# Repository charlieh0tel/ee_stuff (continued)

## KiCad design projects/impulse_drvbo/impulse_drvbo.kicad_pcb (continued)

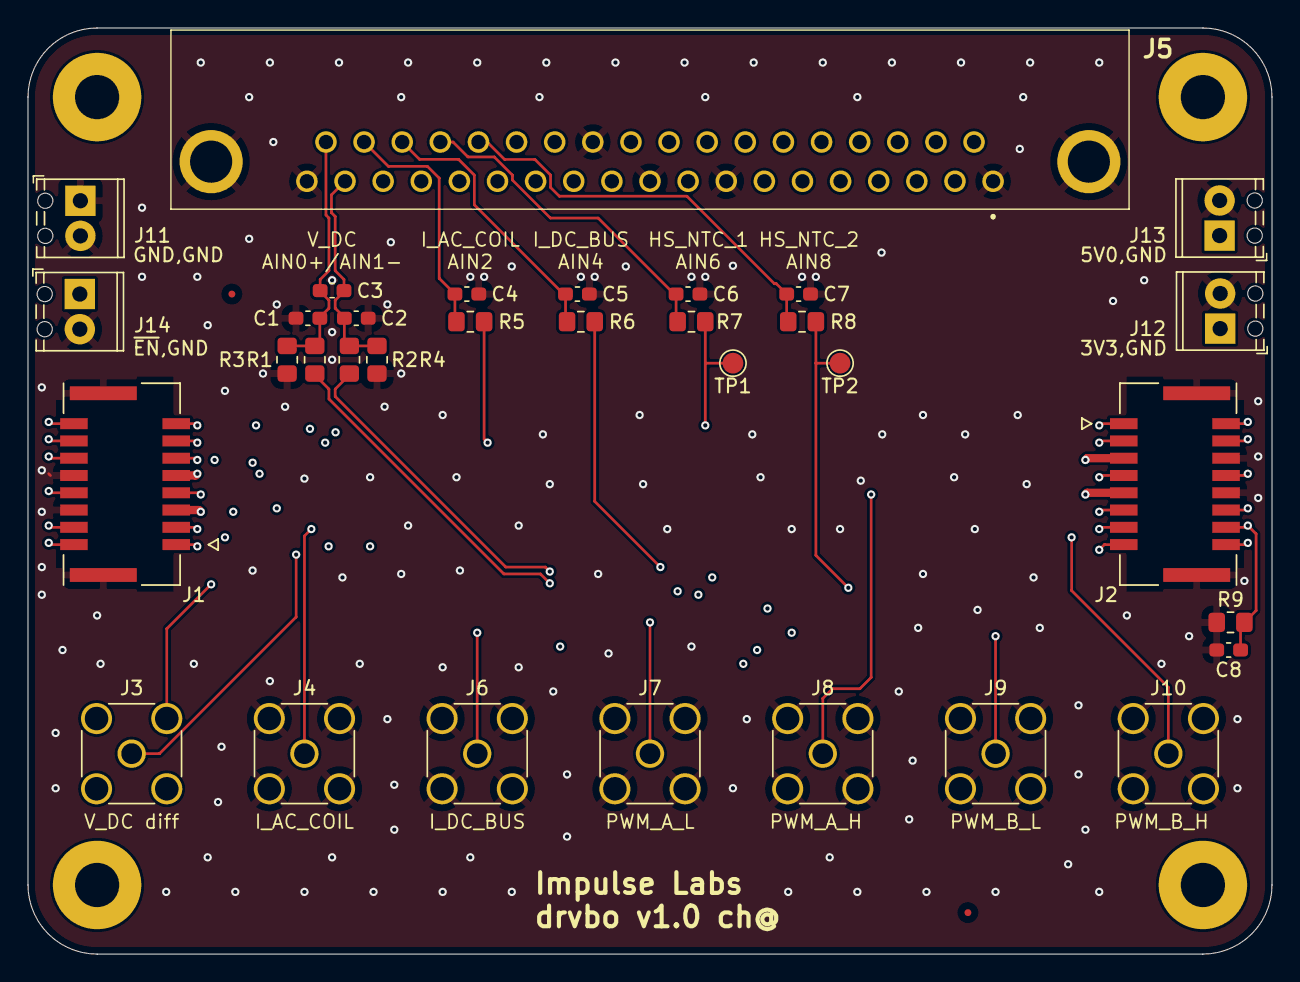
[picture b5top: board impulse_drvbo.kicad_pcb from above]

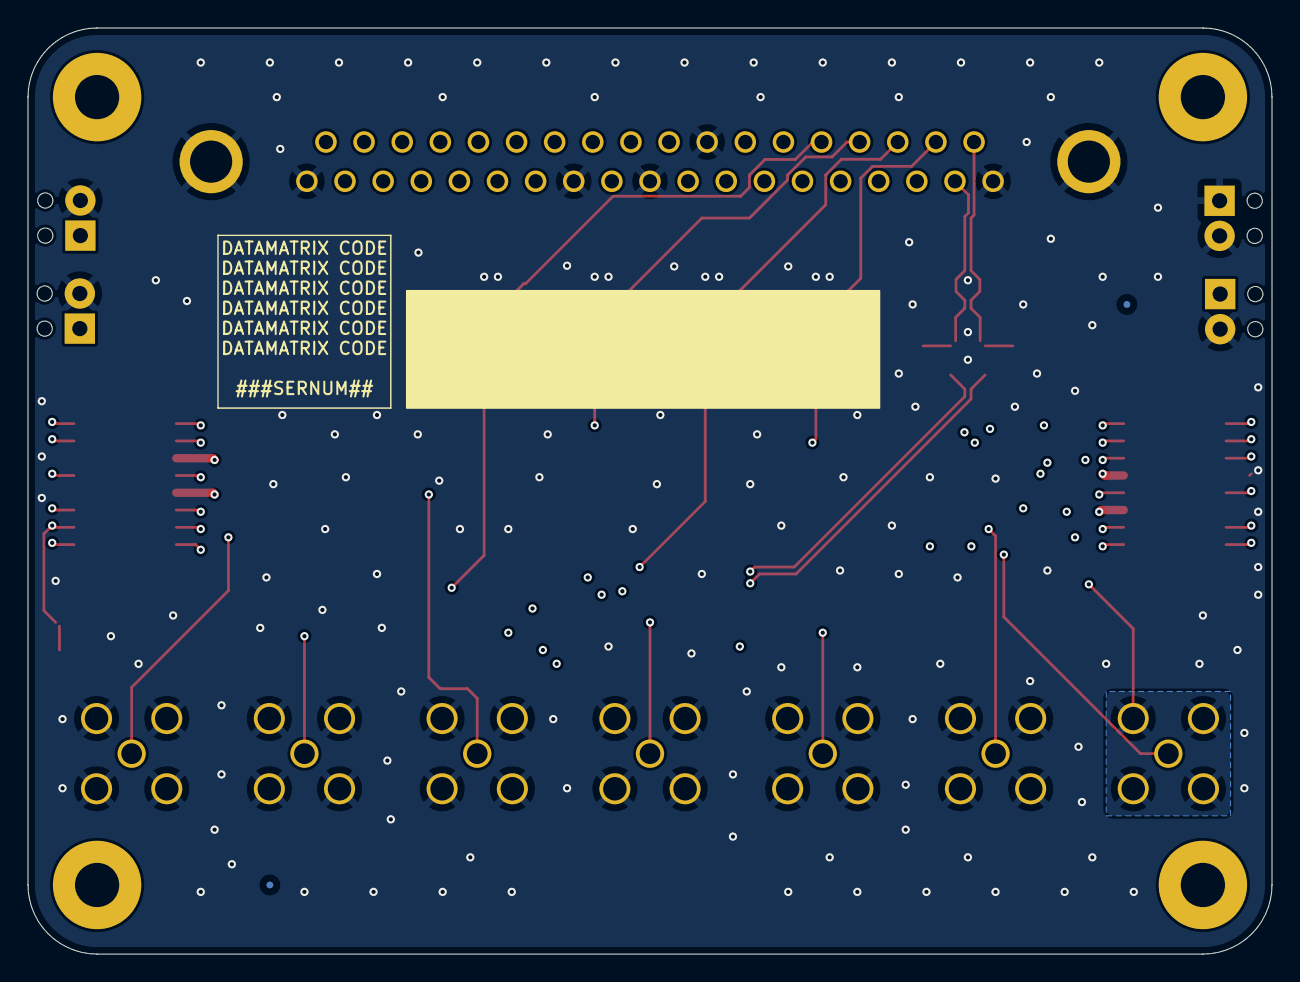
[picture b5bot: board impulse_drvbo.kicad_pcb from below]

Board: 4 copper layers, 90.0 x 67.0 mm, 41 parts (2 on the bottom side), 21 nets.

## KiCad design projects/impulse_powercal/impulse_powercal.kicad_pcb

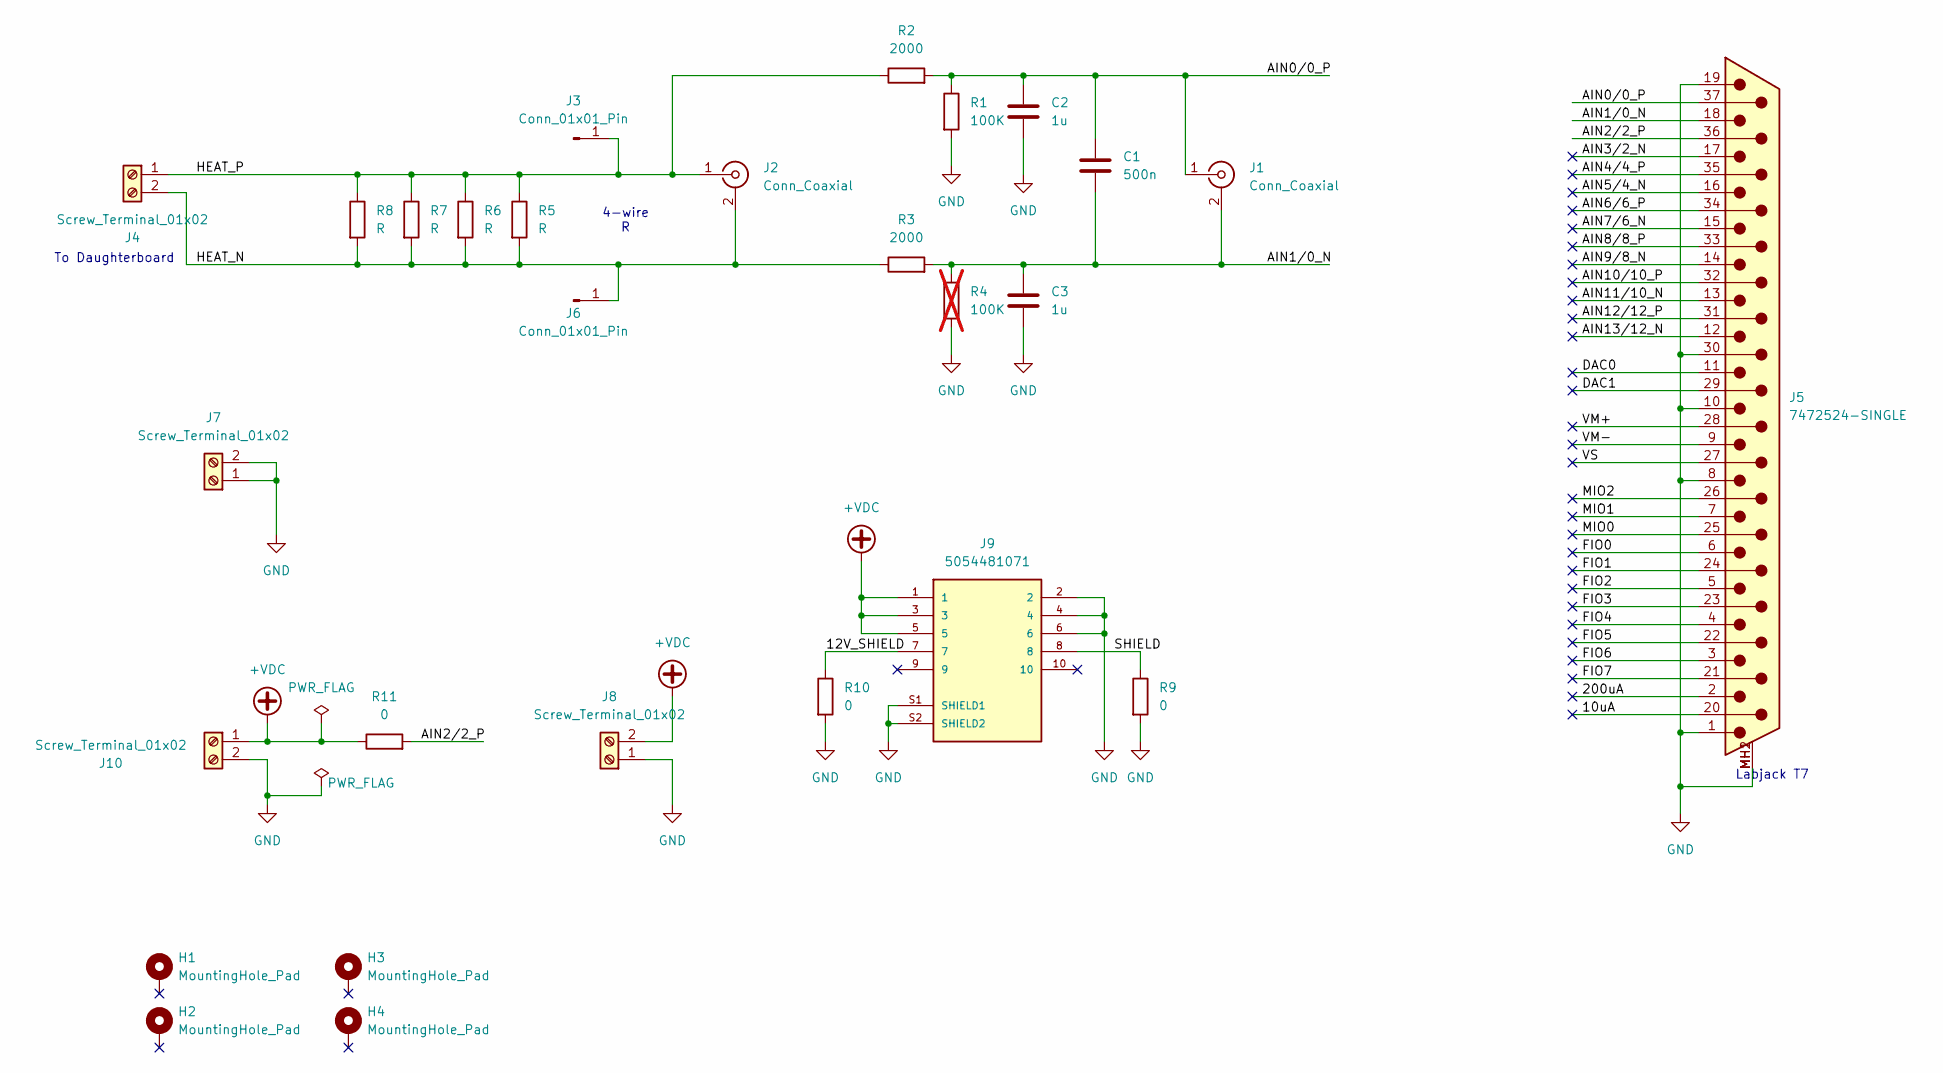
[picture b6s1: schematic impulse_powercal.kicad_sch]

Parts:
C1: 500n; C_0603_1608Metric_Pad1.08x0.95mm_HandSolder; LCSC C513577
C2, C3: 1u; C_0603_1608Metric_Pad1.08x0.95mm_HandSolder; LCSC C5199872
H1, H2, H3, H4: MountingHole_Pad; MountingHole_3.2mm_M3_Pad
J1, J2: Conn_Coaxial; SMA_Amphenol_132291-12_Vertical
J3, J6: Conn_01x01_Pin; 2.5sqmm_D2.5mm
J4, J7, J8: Screw_Terminal_01x02; TerminalBlock_Phoenix_MPT-0,5-2-2.54_1x02_P2.54mm_Horizontal
J5: 7472524-SINGLE; 7472524
J9: 5054481071; MOLEX_5054481071; PARTREV B; LCSC C5367647
J10: Screw_Terminal_01x02; TerminalBlock_Phoenix_MKDS-3-2-5.08_1x02_P5.08mm_Horizontal
R1: 100K; R_0805_2012Metric_Pad1.20x1.40mm_HandSolder
R2, R3: 2000; R_0805_2012Metric_Pad1.20x1.40mm_HandSolder
R4: 100K; R_0805_2012Metric_Pad1.20x1.40mm_HandSolder; not fitted
R5, R6, R7, R8: R; R_2512_6332Metric_Pad1.40x3.35mm_HandSolder
R9, R10, R11: 0; R_0805_2012Metric_Pad1.20x1.40mm_HandSolder

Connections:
+VDC: J8.2, J9.1, J9.3, J9.5, J10.1, R11.1
/10uA: J5.20
/12V_SHIELD: J9.7, R10.1
/200uA: J5.2
/AIN0/0_P: C1.1, C2.1, J1.1 (In), J5.37, R1.1, R2.2
/AIN1/0_N: C1.2, C3.1, J1.2 (Ext), J5.18, R3.2, R4.1
/AIN2/2_P: J5.36, R11.2
/AIN3/2_N: J5.17
/AIN4/4_P: J5.35
/AIN5/4_N: J5.16
/AIN6/6_P: J5.34
/AIN7/6_N: J5.15
/AIN8/8_P: J5.33
/AIN9/8_N: J5.14
/AIN10/10_P: J5.32
/AIN11/10_N: J5.13
/AIN12/12_P: J5.31
/AIN13/12_N: J5.12
/DAC0: J5.11
/DAC1: J5.29
/FIO0: J5.6
/FIO1: J5.24
/FIO2: J5.5
/FIO3: J5.23
/FIO4: J5.4
/FIO5: J5.22
/FIO6: J5.3
/FIO7: J5.21
/HEAT_N: J2.2 (Ext), J4.2, J6.1, R3.1, R5.2, R6.2, R7.2, R8.2
/HEAT_P: J2.1 (In), J3.1, J4.1, R2.1, R5.1, R6.1, R7.1, R8.1
/MIO0: J5.25
/MIO1: J5.7
/MIO2: J5.26
/SHIELD: J9.8, R9.1
/VM+: J5.28
/VM-: J5.9
/VS: J5.27
GND: C2.2, C3.2, J5.1, J5.8, J5.10, J5.19, J5.30, J5.MH1 (PAD), J5.MH2 (PAD), J7.1, J7.2, J8.1, J9.2, J9.4, J9.6, J9.S1 (SHIELD1), J9.S2 (SHIELD2), J10.2, R1.2, R4.2, R9.2, R10.2

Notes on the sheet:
4-wire R
Labjack T7
To Daughterboard

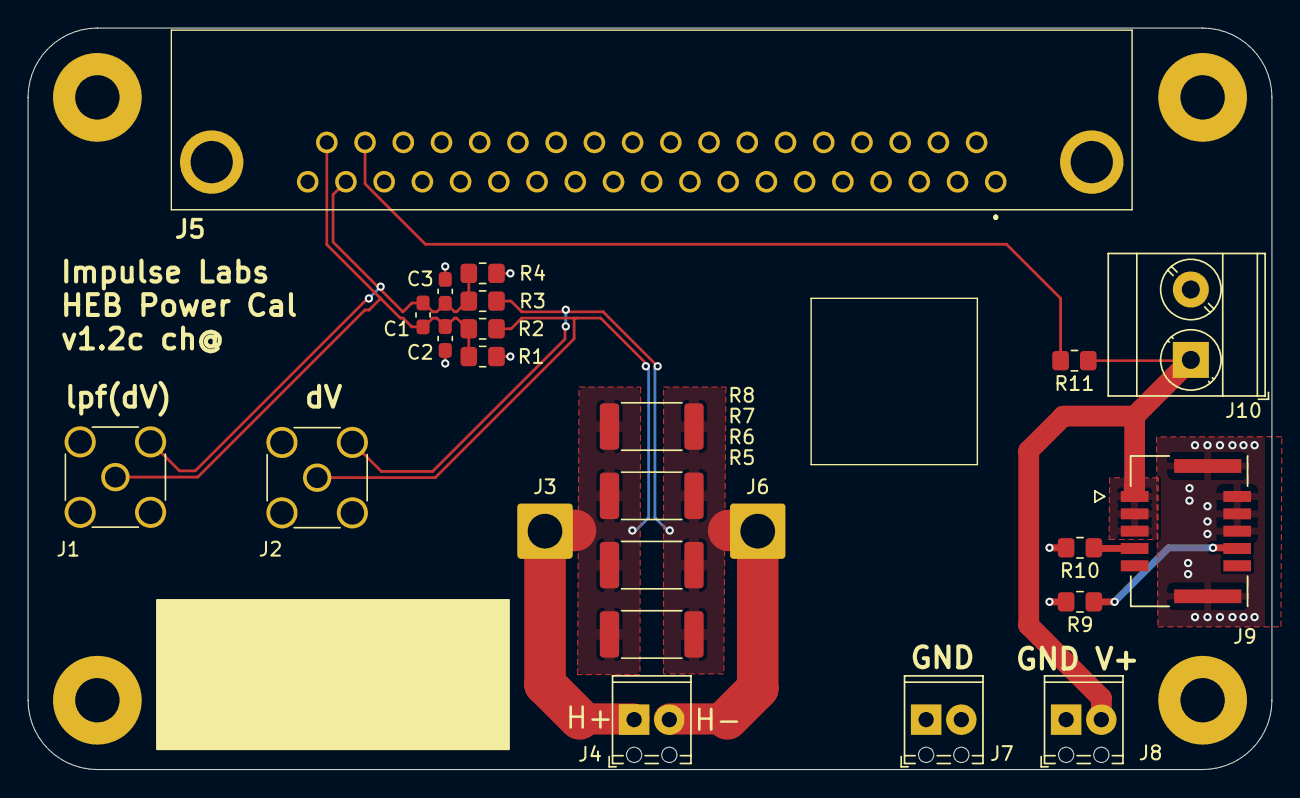
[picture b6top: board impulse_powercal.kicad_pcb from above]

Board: 2 copper layers, 89.8 x 53.5 mm, 28 parts (0 on the bottom side), 9 nets.

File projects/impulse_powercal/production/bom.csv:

Designator,Footprint,Quantity,Value,LCSC Part #
C1,0603,1,500n,C513577
"C2, C3",0603,2,1u, C5199872
"J1, J2",SMA_Amphenol_132291-12_Vertical,2,Conn_Coaxial,
J10,TerminalBlock_Phoenix_MKDS-3-2-5.08_1x02_P5.08mm_Horizontal,1,Screw_Terminal_01x02,
"J3, J6",SolderWire-2.5sqmm_1x01_D2.4mm_OD3.6mm,2,Conn_01x01_Pin,
"J4, J7, J8","TerminalBlock_Phoenix_MPT-0,5-2-2.54_1x02_P2.54mm_Horizontal",3,Screw_Terminal_01x02,
J5,7472524,1,7472524-SINGLE,
J9,MOLEX_5054481071,1,5054481071,
R1,0805,1,100K,
"R10, R11, R9",0805,3,0,
"R2, R3",0805,2,2000,
"R5, R6, R7, R8",2512,4,R,

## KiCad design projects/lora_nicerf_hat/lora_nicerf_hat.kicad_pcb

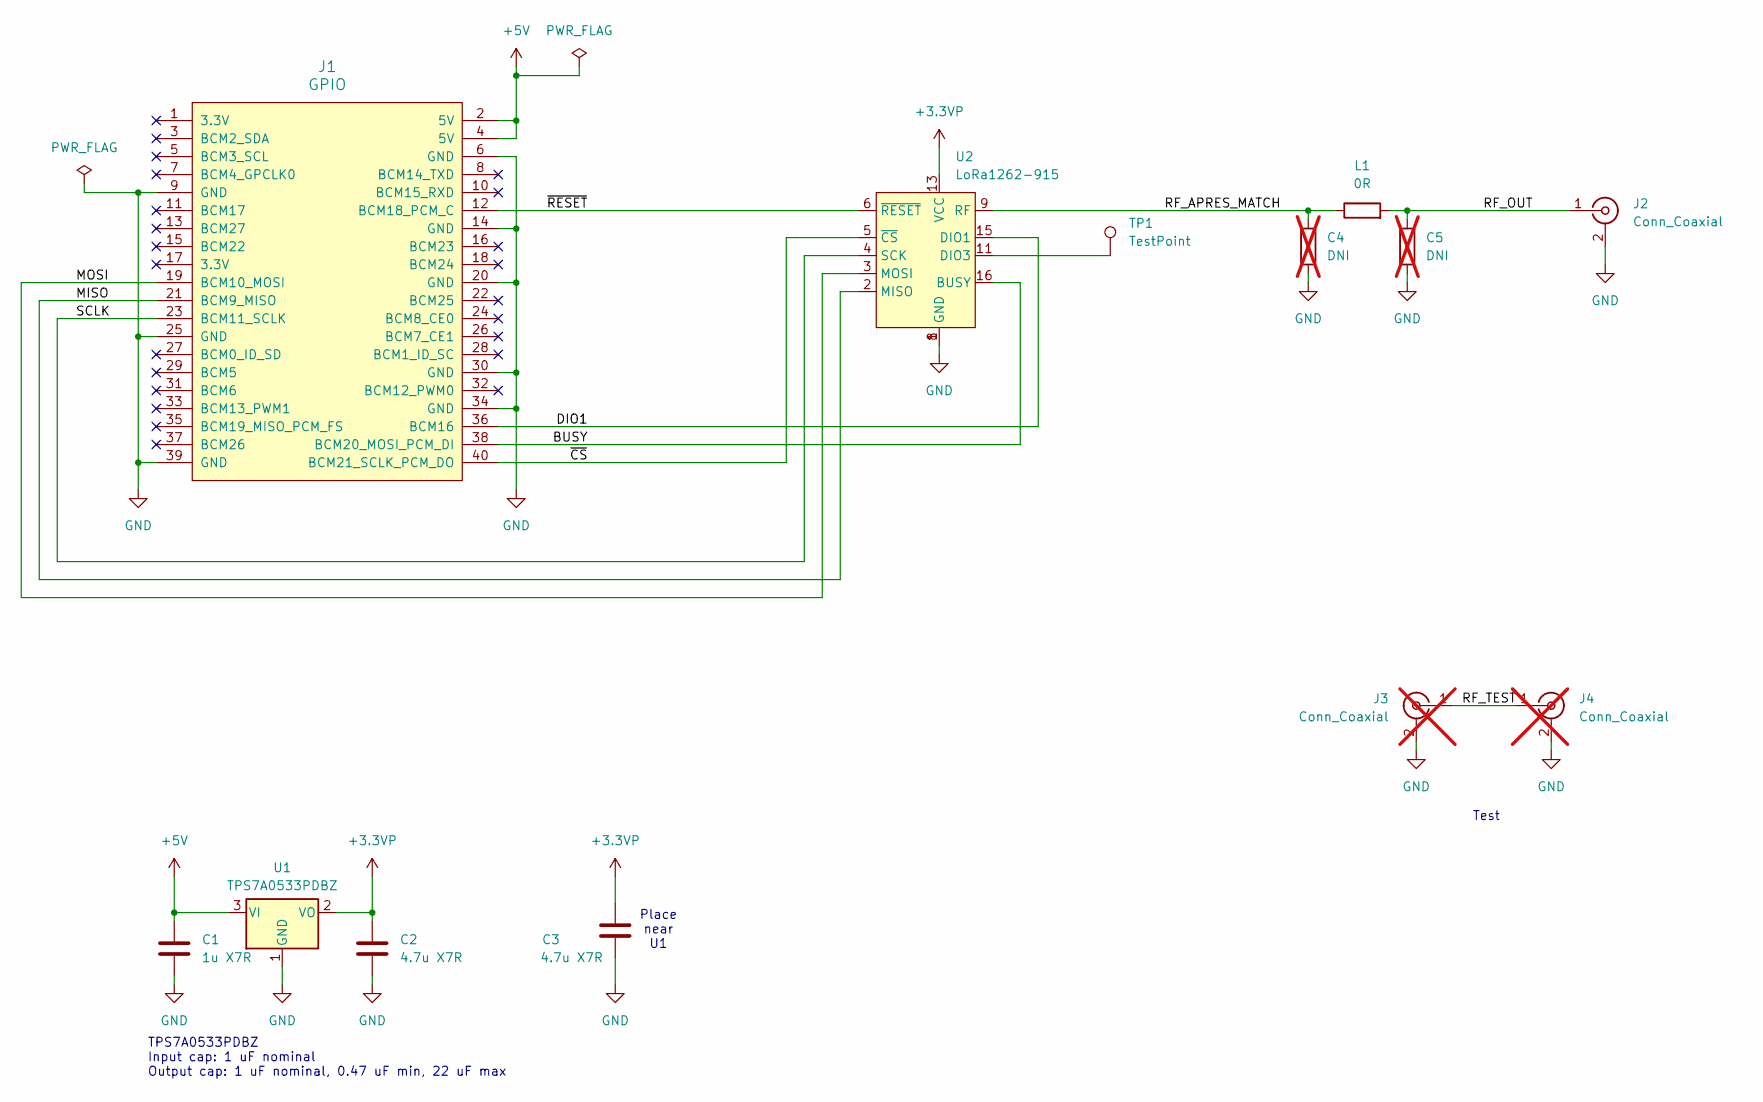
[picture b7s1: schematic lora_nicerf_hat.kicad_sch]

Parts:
C1: 1u X7R; C_0805_2012Metric_Pad1.18x1.45mm_HandSolder
C2, C3: 4.7u X7R; C_0805_2012Metric_Pad1.18x1.45mm_HandSolder
C4, C5: DNI; R_0402_1005Metric; not fitted
J1: GPIO; Harwin M20-7812045
J2: Conn_Coaxial; SMA_Molex-73391-0070_Vertical
J3, J4: Conn_Coaxial; U.FL_Hirose_U.FL-R-SMT-1_Vertical; not fitted
L1: 0R; R_0402_1005Metric
TP1: TestPoint; TestPoint_THTPad_2.0x2.0mm_Drill1.0mm
U1: TPS7A0533PDBZ; SOT-23
U2: LoRa1262-915; G-Nice_RF_LoRa1262-915

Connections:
+3.3VP: C2.1, C3.1, U1.2 (VO), U2.13 (VCC)
+5V: C1.1, J1.2 (5V), J1.4 (5V), U1.3 (VI)
/BUSY: J1.38 (BCM20_MOSI_PCM_DI), U2.16 (BUSY)
/DIO1: J1.36 (BCM16), U2.15 (DIO1)
/MISO: J1.21 (BCM9_MISO), U2.2 (MISO)
/MOSI: J1.19 (BCM10_MOSI), U2.3 (MOSI)
/RF_APRES_MATCH: C4.1, L1.1, U2.9 (RF)
/RF_OUT: C5.1, J2.1 (In), L1.2
/RF_TEST: J3.1 (In), J4.1 (In)
/SCLK: J1.23 (BCM11_SCLK), U2.4 (SCK)
/~CS: J1.40 (BCM21_SCLK_PCM_DO), U2.5 (~CS)
/~RESET: J1.12 (BCM18_PCM_C), U2.6 (~RESET)
GND: C1.2, C2.2, C3.2, C4.2, C5.2, J1.6 (GND), J1.9 (GND), J1.14 (GND), J1.20 (GND), J1.25 (GND), J1.30 (GND), J1.34 (GND), J1.39 (GND), J2.2 (Ext), J3.2 (Ext), J4.2 (Ext), U1.1 (GND), U2.1 (GND), U2.8 (GND), U2.10 (GND)
unnamed: TP1.1, U2.11 (DIO3)

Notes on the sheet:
Test
Place near U1
TPS7A0533PDBZ Input cap: 1 uF nominal Output cap: 1 uF nominal, 0.47 uF min, 22 uF max

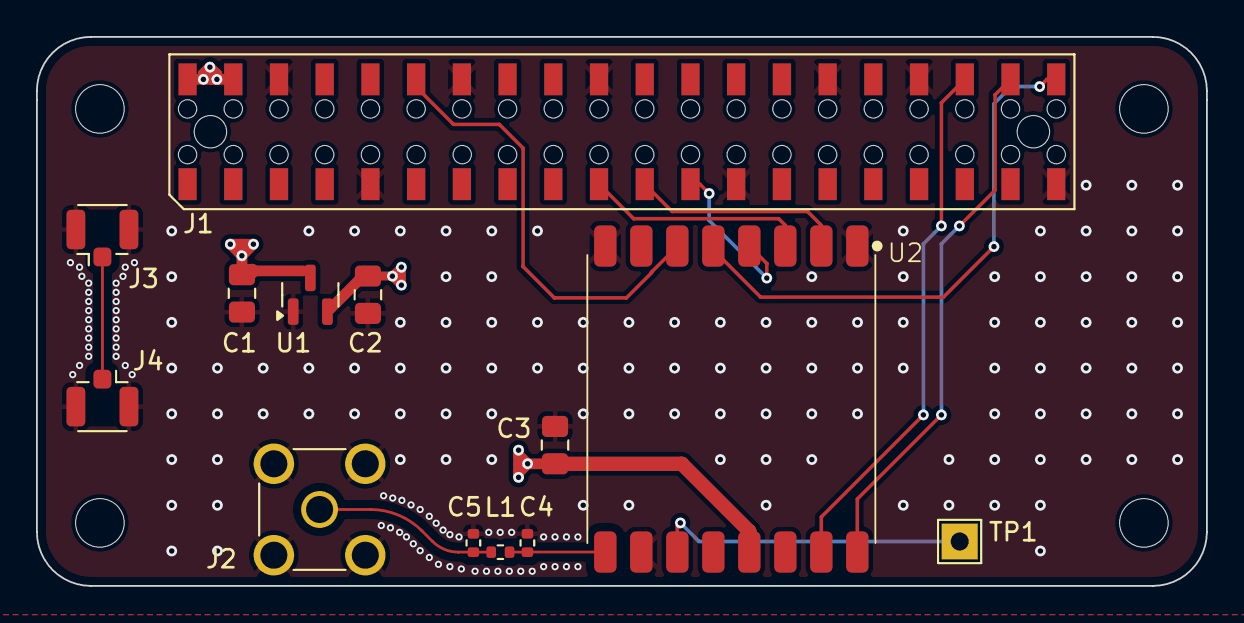
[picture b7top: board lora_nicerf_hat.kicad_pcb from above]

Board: 4 copper layers, 65.0 x 30.5 mm, 17 parts (0 on the bottom side), 14 nets.

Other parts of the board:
MH1, MH2, MH3, MH4: MountingHole_2.7mm_M2.5

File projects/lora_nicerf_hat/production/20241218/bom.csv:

Designator,Footprint,Quantity,Value,LCSC Part #
C1,0805,1,1u X7R,
"C2, C3",0805,2,4.7u X7R,
J1,Harwin M20-7812045,1,GPIO,C42411761
J2,SMA_Molex-73391-0070_Vertical,1,Conn_Coaxial,
L1,0402,1,0R,
TP1,TestPoint_THTPad_2.0x2.0mm_Drill1.0mm,1,TestPoint,
U1,SOT-23,1,TPS7A0533PDBZ,
U2,G-Nice_RF_LoRa1262-915,1,LoRa1262-915,C5356643
